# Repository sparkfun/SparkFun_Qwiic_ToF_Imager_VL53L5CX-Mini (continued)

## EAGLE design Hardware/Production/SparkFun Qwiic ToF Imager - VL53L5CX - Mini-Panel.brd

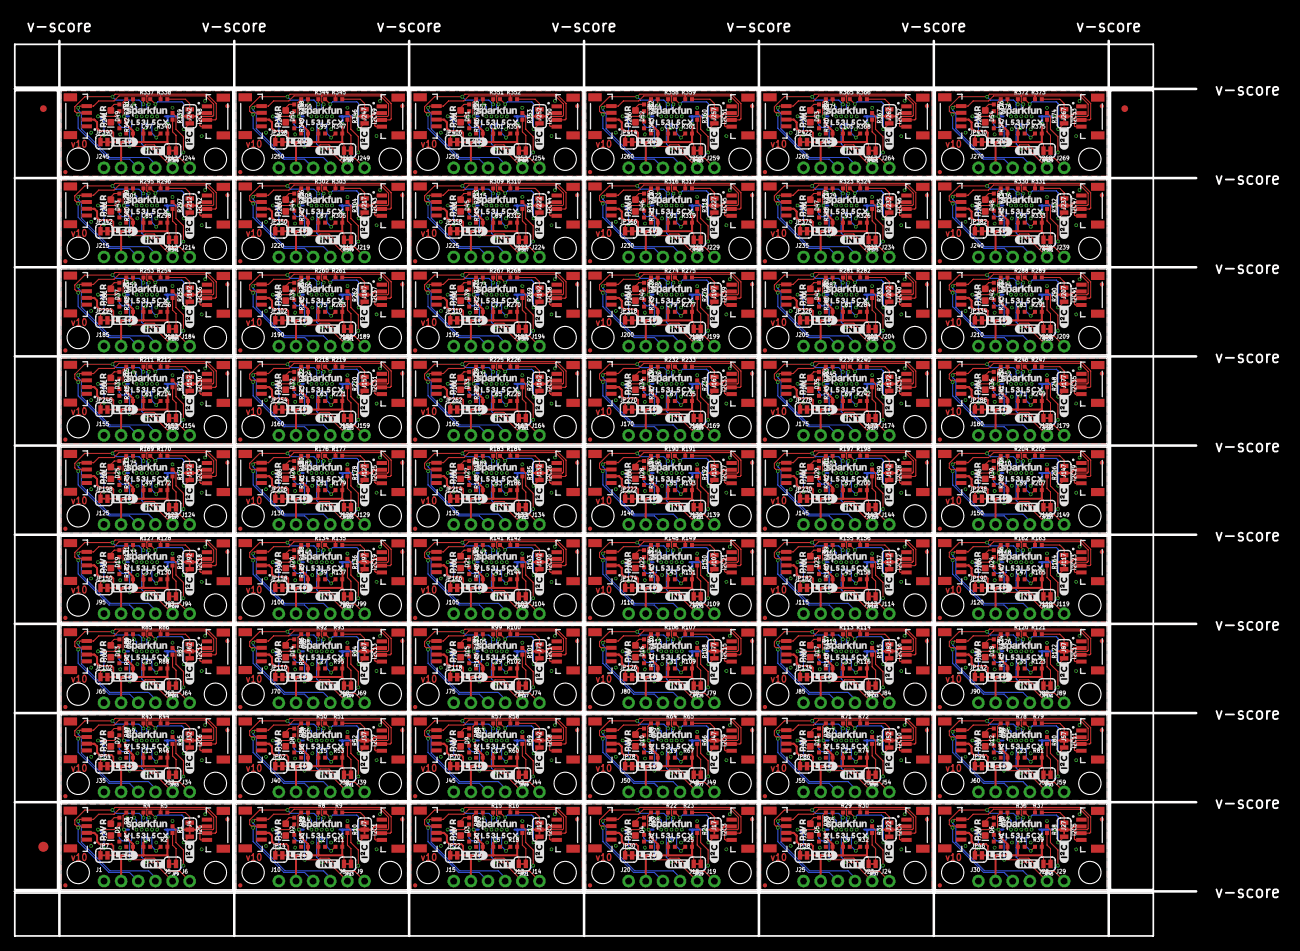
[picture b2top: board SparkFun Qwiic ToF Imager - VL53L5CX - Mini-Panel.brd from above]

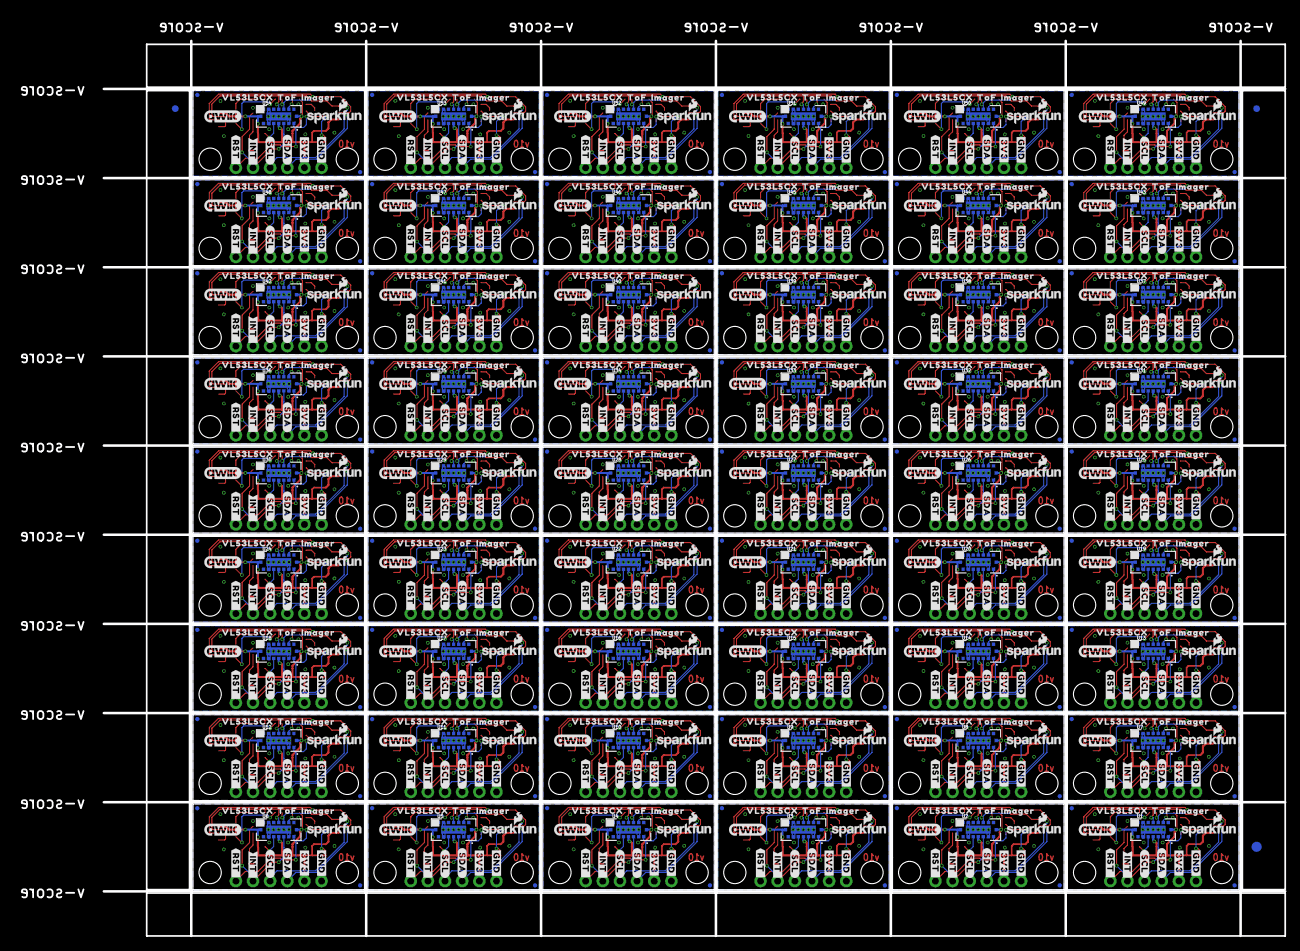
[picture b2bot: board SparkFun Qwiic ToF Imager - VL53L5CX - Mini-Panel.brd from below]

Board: 2 copper layers, 175.0 x 132.6 mm, 2274 parts (759 on the bottom side), 702 nets.

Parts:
C1, C3, C6, C8, C10, C12, C14, C16, C18, C20, C22, C24, C26, C28, C30, C32, C34, C36, C38, C40, C42, C44, C46, C48, C50, C52, C54, C56, C58, C60, C62, C64, C66, C68, C70, C72, C74, C76, C78, C80, C82, C84, C86, C88, C90, C92, C94, C96, C98, C100, C102, C104, C106, C108: 4.7uF; 0402-TIGHT
C2, C4, C5, C7, C9, C11, C13, C15, C17, C19, C21, C23, C25, C27, C29, C31, C33, C35, C37, C39, C41, C43, C45, C47, C49, C51, C53, C55, C57, C59, C61, C63, C65, C67, C69, C71, C73, C75, C77, C79, C81, C83, C85, C87, C89, C91, C93, C95, C97, C99, C101, C103, C105, C107: 0.1uF; 0402-TIGHT
D1, D2, D3, D4, D5, D6, D7, D8, D9, D10, D11, D12, D13, D14, D15, D16, D17, D18, D19, D20, D21, D22, D23, D24, D25, D26, D27, D28, D29, D30, D31, D32, D33, D34, D35, D36, D37, D38, D39, D40, D41, D42, D43, D44, D45, D46, D47, D48, D49, D50, D51, D52, D53, D54: RED; LED-0603
E$1, E$2, E$3, E$4: FIDUCIAL-1X2
E$5, E$6: FIDUCIAL-1.5X3
I2C, I2C1, I2C2, I2C3, I2C4, I2C5, I2C6, I2C7, I2C8, I2C9, I2C10, I2C11, I2C12, I2C13, I2C14, I2C15, I2C16, I2C17, I2C18, I2C19, I2C20, I2C21, I2C22, I2C23, I2C24, I2C25, I2C26, I2C27, I2C28, I2C29, I2C30, I2C31, I2C32, I2C33, I2C34, I2C35, I2C36, I2C37, I2C38, I2C39, I2C40, I2C41, I2C42, I2C43, I2C44, I2C45, I2C46, I2C47, I2C48, I2C49, I2C50, I2C51, I2C52, I2C53: JUMPER-SMT_3_2-NC_TRACE_SILK; SMT-JUMPER_3_2-NC_TRACE_SILK
J1, J10, J15, J20, J25, J30, J35, J40, J45, J50, J55, J60, J65, J70, J75, J80, J85, J90, J95, J100, J105, J110, J115, J120, J125, J130, J135, J140, J145, J150, J155, J160, J165, J170, J175, J180, J185, J190, J195, J200, J205, J210, J215, J220, J225, J230, J235, J240, J245, J250, J255, J260, J265, J270: 1X04_NO_SILK
J2, J3, J4, J7, J11, J12, J16, J17, J21, J22, J26, J27, J31, J32, J36, J37, J41, J42, J46, J47, J51, J52, J56, J57, J61, J62, J66, J67, J71, J72, J76, J77, J81, J82, J86, J87, J91, J92, J96, J97, J101, J102, J106, J107, J111, J112, J116, J117, J121, J122, J126, J127, J131, J132, J136, J137, J141, J142, J146, J147, J151, J152, J156, J157, J161, J162, J166, J167, J171, J172, J176, J177, J181, J182, J186, J187, J191, J192, J196, J197, J201, J202, J206, J207, J211, J212, J216, J217, J221, J222, J226, J227, J231, J232, J236, J237, J241, J242, J246, J247, J251, J252, J256, J257, J261, J262, J266, J267: Vertical Qwiic Connector; JST04_1MM_VERT
J5, J6, J8, J9, J13, J14, J18, J19, J23, J24, J28, J29, J33, J34, J38, J39, J43, J44, J48, J49, J53, J54, J58, J59, J63, J64, J68, J69, J73, J74, J78, J79, J83, J84, J88, J89, J93, J94, J98, J99, J103, J104, J108, J109, J113, J114, J118, J119, J123, J124, J128, J129, J133, J134, J138, J139, J143, J144, J148, J149, J153, J154, J158, J159, J163, J164, J168, J169, J173, J174, J178, J179, J183, J184, J188, J189, J193, J194, J198, J199, J203, J204, J208, J209, J213, J214, J218, J219, J223, J224, J228, J229, J233, J234, J238, J239, J243, J244, J248, J249, J253, J254, J258, J259, J263, J264, J268, J269: 1X01_NO_SILK
JP1, JP2, JP3, JP4, JP5, JP6, JP8, JP12, JP17, JP18, JP19, JP20, JP25, JP26, JP27, JP28, JP33, JP34, JP35, JP36, JP41, JP42, JP43, JP44, JP49, JP50, JP51, JP52, JP57, JP58, JP59, JP60, JP65, JP66, JP67, JP68, JP73, JP74, JP75, JP76, JP81, JP82, JP83, JP84, JP89, JP90, JP91, JP92, JP97, JP98, JP99, JP100, JP105, JP106, JP107, JP108, JP113, JP114, JP115, JP116, JP121, JP122, JP123, JP124, JP129, JP130, JP131, JP132, JP137, JP138, JP139, JP140, JP145, JP146, JP147, JP148, JP153, JP154, JP155, JP156, JP161, JP162, JP163, JP164, JP169, JP170, JP171, JP172, JP177, JP178, JP179, JP180, JP185, JP186, JP187, JP188, JP193, JP194, JP195, JP196, JP201, JP202, JP203, JP204, JP209, JP210, JP211, JP212, JP217, JP218, JP219, JP220, JP225, JP226, JP227, JP228, JP233, JP234, JP235, JP236, JP241, JP242, JP243, JP244, JP249, JP250, JP251, JP252, JP257, JP258, JP259, JP260, JP265, JP266, JP267, JP268, JP273, JP274, JP275, JP276, JP281, JP282, JP283, JP284, JP289, JP290, JP291, JP292, JP297, JP298, JP299, JP300, JP305, JP306, JP307, JP308, JP313, JP314, JP315, JP316, JP321, JP322, JP323, JP324, JP329, JP330, JP331, JP332, JP337, JP338, JP339, JP340, JP345, JP346, JP347, JP348, JP353, JP354, JP355, JP356, JP361, JP362, JP363, JP364, JP369, JP370, JP371, JP372, JP377, JP378, JP379, JP380, JP385, JP386, JP387, JP388, JP393, JP394, JP395, JP396, JP401, JP402, JP403, JP404, JP409, JP410, JP411, JP412, JP417, JP418, JP419, JP420, JP425, JP426, JP427, JP428: FIDUCIALUFIDUCIAL; FIDUCIAL-MICRO
JP7, JP14, JP22, JP30, JP38, JP46, JP54, JP62, JP70, JP78, JP86, JP94, JP102, JP110, JP118, JP126, JP134, JP142, JP150, JP158, JP166, JP174, JP182, JP190, JP198, JP206, JP214, JP222, JP230, JP238, JP246, JP254, JP262, JP270, JP278, JP286, JP294, JP302, JP310, JP318, JP326, JP334, JP342, JP350, JP358, JP366, JP374, JP382, JP390, JP398, JP406, JP414, JP422, JP430: PWR_LED; SMT-JUMPER_2_NC_TRACE_SILK
JP9, JP13, JP21, JP29, JP37, JP45, JP53, JP61, JP69, JP77, JP85, JP93, JP101, JP109, JP117, JP125, JP133, JP141, JP149, JP157, JP165, JP173, JP181, JP189, JP197, JP205, JP213, JP221, JP229, JP237, JP245, JP253, JP261, JP269, JP277, JP285, JP293, JP301, JP309, JP317, JP325, JP333, JP341, JP349, JP357, JP365, JP373, JP381, JP389, JP397, JP405, JP413, JP421, JP429: INT; SMT-JUMPER_2_NC_TRACE_SILK
JP10, JP11, JP15, JP16, JP23, JP24, JP31, JP32, JP39, JP40, JP47, JP48, JP55, JP56, JP63, JP64, JP71, JP72, JP79, JP80, JP87, JP88, JP95, JP96, JP103, JP104, JP111, JP112, JP119, JP120, JP127, JP128, JP135, JP136, JP143, JP144, JP151, JP152, JP159, JP160, JP167, JP168, JP175, JP176, JP183, JP184, JP191, JP192, JP199, JP200, JP207, JP208, JP215, JP216, JP223, JP224, JP231, JP232, JP239, JP240, JP247, JP248, JP255, JP256, JP263, JP264, JP271, JP272, JP279, JP280, JP287, JP288, JP295, JP296, JP303, JP304, JP311, JP312, JP319, JP320, JP327, JP328, JP335, JP336, JP343, JP344, JP351, JP352, JP359, JP360, JP367, JP368, JP375, JP376, JP383, JP384, JP391, JP392, JP399, JP400, JP407, JP408, JP415, JP416, JP423, JP424, JP431, JP432: STAND-OFF
LOGO1, LOGO6, LOGO9, LOGO12, LOGO15, LOGO18, LOGO21, LOGO24, LOGO27, LOGO30, LOGO33, LOGO36, LOGO39, LOGO42, LOGO45, LOGO48, LOGO51, LOGO54, LOGO57, LOGO60, LOGO63, LOGO66, LOGO69, LOGO72, LOGO75, LOGO78, LOGO81, LOGO84, LOGO87, LOGO90, LOGO93, LOGO96, LOGO99, LOGO102, LOGO105, LOGO108, LOGO111, LOGO114, LOGO117, LOGO120, LOGO123, LOGO126, LOGO129, LOGO132, LOGO135, LOGO138, LOGO141, LOGO144, LOGO147, LOGO150, LOGO153, LOGO156, LOGO159, LOGO162: SFE_LOGO_NAME_FLAME8_MM; SFE_LOGO_NAME_FLAME_8MM
LOGO2, LOGO3, LOGO7, LOGO10, LOGO13, LOGO16, LOGO19, LOGO22, LOGO25, LOGO28, LOGO31, LOGO34, LOGO37, LOGO40, LOGO43, LOGO46, LOGO49, LOGO52, LOGO55, LOGO58, LOGO61, LOGO64, LOGO67, LOGO70, LOGO73, LOGO76, LOGO79, LOGO82, LOGO85, LOGO88, LOGO91, LOGO94, LOGO97, LOGO100, LOGO103, LOGO106, LOGO109, LOGO112, LOGO115, LOGO118, LOGO121, LOGO124, LOGO127, LOGO130, LOGO133, LOGO136, LOGO139, LOGO142, LOGO145, LOGO148, LOGO151, LOGO154, LOGO157, LOGO160: QWIIC_LOGO_CONNECTOR; QWIIC_5.5MM
LOGO4, LOGO5, LOGO8, LOGO11, LOGO14, LOGO17, LOGO20, LOGO23, LOGO26, LOGO29, LOGO32, LOGO35, LOGO38, LOGO41, LOGO44, LOGO47, LOGO50, LOGO53, LOGO56, LOGO59, LOGO62, LOGO65, LOGO68, LOGO71, LOGO74, LOGO77, LOGO80, LOGO83, LOGO86, LOGO89, LOGO92, LOGO95, LOGO98, LOGO101, LOGO104, LOGO107, LOGO110, LOGO113, LOGO116, LOGO119, LOGO122, LOGO125, LOGO128, LOGO131, LOGO134, LOGO137, LOGO140, LOGO143, LOGO146, LOGO149, LOGO152, LOGO155, LOGO158, LOGO161: SFE_LOGO_NAME6_MM; SFE_LOGO_NAME_6MM
R1, R2, R6, R7, R10, R11, R13, R14, R17, R18, R20, R21, R24, R25, R27, R28, R31, R32, R34, R35, R38, R39, R41, R42, R45, R46, R48, R49, R52, R53, R55, R56, R59, R60, R62, R63, R66, R67, R69, R70, R73, R74, R76, R77, R80, R81, R83, R84, R87, R88, R90, R91, R94, R95, R97, R98, R101, R102, R104, R105, R108, R109, R111, R112, R115, R116, R118, R119, R122, R123, R125, R126, R129, R130, R132, R133, R136, R137, R139, R140, R143, R144, R146, R147, R150, R151, R153, R154, R157, R158, R160, R161, R164, R165, R167, R168, R171, R172, R174, R175, R178, R179, R181, R182, R185, R186, R188, R189, R192, R193, R195, R196, R199, R200, R202, R203, R206, R207, R209, R210, R213, R214, R216, R217, R220, R221, R223, R224, R227, R228, R230, R231, R234, R235, R237, R238, R241, R242, R244, R245, R248, R249, R251, R252, R255, R256, R258, R259, R262, R263, R265, R266, R269, R270, R272, R273, R276, R277, R279, R280, R283, R284, R286, R287, R290, R291, R293, R294, R297, R298, R300, R301, R304, R305, R307, R308, R311, R312, R314, R315, R318, R319, R321, R322, R325, R326, R328, R329, R332, R333, R335, R336, R339, R340, R342, R343, R346, R347, R349, R350, R353, R354, R356, R357, R360, R361, R363, R364, R367, R368, R370, R371, R374, R375, R377, R378: 47k; 0402-TIGHT
R3, R12, R19, R26, R33, R40, R47, R54, R61, R68, R75, R82, R89, R96, R103, R110, R117, R124, R131, R138, R145, R152, R159, R166, R173, R180, R187, R194, R201, R208, R215, R222, R229, R236, R243, R250, R257, R264, R271, R278, R285, R292, R299, R306, R313, R320, R327, R334, R341, R348, R355, R362, R369, R376: 1k; 0402-TIGHT
R4, R5, R8, R9, R15, R16, R22, R23, R29, R30, R36, R37, R43, R44, R50, R51, R57, R58, R64, R65, R71, R72, R78, R79, R85, R86, R92, R93, R99, R100, R106, R107, R113, R114, R120, R121, R127, R128, R134, R135, R141, R142, R148, R149, R155, R156, R162, R163, R169, R170, R176, R177, R183, R184, R190, R191, R197, R198, R204, R205, R211, R212, R218, R219, R225, R226, R232, R233, R239, R240, R246, R247, R253, R254, R260, R261, R267, R268, R274, R275, R281, R282, R288, R289, R295, R296, R302, R303, R309, R310, R316, R317, R323, R324, R330, R331, R337, R338, R344, R345, R351, R352, R358, R359, R365, R366, R372, R373: 2.2k; 0402-TIGHT
U1, U2, U3, U4, U5, U6, U7, U8, U9, U10, U11, U12, U13, U14, U15, U16, U17, U18, U19, U20, U21, U22, U23, U24, U25, U26, U27, U28, U29, U30, U31, U32, U33, U34, U35, U36, U37, U38, U39, U40, U41, U42, U43, U44, U45, U46, U47, U48, U49, U50, U51, U52, U53, U54: VL53L5CX
U$1, U$23, U$40, U$54, U$68, U$82, U$96, U$110, U$124, U$138, U$152, U$166, U$180, U$194, U$208, U$222, U$236, U$250, U$264, U$278, U$292, U$306, U$320, U$334, U$348, U$362, U$376, U$390, U$404, U$418, U$432, U$446, U$460, U$474, U$488, U$502, U$516, U$530, U$544, U$558, U$572, U$586, U$600, U$614, U$628, U$642, U$656, U$670, U$684, U$698, U$712, U$726, U$740, U$754: VL53L5CX_0
U$2, U$26, U$41, U$55, U$69, U$83, U$97, U$111, U$125, U$139, U$153, U$167, U$181, U$195, U$209, U$223, U$237, U$251, U$265, U$279, U$293, U$307, U$321, U$335, U$349, U$363, U$377, U$391, U$405, U$419, U$433, U$447, U$461, U$475, U$489, U$503, U$517, U$531, U$545, U$559, U$573, U$587, U$601, U$615, U$629, U$643, U$657, U$671, U$685, U$699, U$713, U$727, U$741, U$755: #LED#0
U$3, U$7, U$29, U$44, U$58, U$72, U$86, U$100, U$114, U$128, U$142, U$156, U$170, U$184, U$198, U$212, U$226, U$240, U$254, U$268, U$282, U$296, U$310, U$324, U$338, U$352, U$366, U$380, U$394, U$408, U$422, U$436, U$450, U$464, U$478, U$492, U$506, U$520, U$534, U$548, U$562, U$576, U$590, U$604, U$618, U$632, U$646, U$660, U$674, U$688, U$702, U$716, U$730, U$744: #3V3#13
U$4, U$10, U$31, U$45, U$59, U$73, U$87, U$101, U$115, U$129, U$143, U$157, U$171, U$185, U$199, U$213, U$227, U$241, U$255, U$269, U$283, U$297, U$311, U$325, U$339, U$353, U$367, U$381, U$395, U$409, U$423, U$437, U$451, U$465, U$479, U$493, U$507, U$521, U$535, U$549, U$563, U$577, U$591, U$605, U$619, U$633, U$647, U$661, U$675, U$689, U$703, U$717, U$731, U$745: PWR12
U$5, U$27, U$42, U$56, U$70, U$84, U$98, U$112, U$126, U$140, U$154, U$168, U$182, U$196, U$210, U$224, U$238, U$252, U$266, U$280, U$294, U$308, U$322, U$336, U$350, U$364, U$378, U$392, U$406, U$420, U$434, U$448, U$462, U$476, U$490, U$504, U$518, U$532, U$546, U$560, U$574, U$588, U$602, U$616, U$630, U$644, U$658, U$672, U$686, U$700, U$714, U$728, U$742, U$756: #INT#0
U$6, U$28, U$30, U$43, U$57, U$71, U$85, U$99, U$113, U$127, U$141, U$155, U$169, U$183, U$197, U$211, U$225, U$239, U$253, U$267, U$281, U$295, U$309, U$323, U$337, U$351, U$365, U$379, U$393, U$407, U$421, U$435, U$449, U$463, U$477, U$491, U$505, U$519, U$533, U$547, U$561, U$575, U$589, U$603, U$617, U$631, U$645, U$659, U$673, U$687, U$701, U$715, U$729, U$743: #GND#62130
U$8, U$11, U$32, U$46, U$60, U$74, U$88, U$102, U$116, U$130, U$144, U$158, U$172, U$186, U$200, U$214, U$228, U$242, U$256, U$270, U$284, U$298, U$312, U$326, U$340, U$354, U$368, U$382, U$396, U$410, U$424, U$438, U$452, U$466, U$480, U$494, U$508, U$522, U$536, U$550, U$564, U$578, U$592, U$606, U$620, U$634, U$648, U$662, U$676, U$690, U$704, U$718, U$732, U$746: #INT_#0
U$9, U$12, U$33, U$47, U$61, U$75, U$89, U$103, U$117, U$131, U$145, U$159, U$173, U$187, U$201, U$215, U$229, U$243, U$257, U$271, U$285, U$299, U$313, U$327, U$341, U$355, U$369, U$383, U$397, U$411, U$425, U$439, U$453, U$467, U$481, U$495, U$509, U$523, U$537, U$551, U$565, U$579, U$593, U$607, U$621, U$635, U$649, U$663, U$677, U$691, U$705, U$719, U$733, U$747: #RST_#1
U$13, U$16, U$34, U$48, U$62, U$76, U$90, U$104, U$118, U$132, U$146, U$160, U$174, U$188, U$202, U$216, U$230, U$244, U$258, U$272, U$286, U$300, U$314, U$328, U$342, U$356, U$370, U$384, U$398, U$412, U$426, U$440, U$454, U$468, U$482, U$496, U$510, U$524, U$538, U$552, U$566, U$580, U$594, U$608, U$622, U$636, U$650, U$664, U$678, U$692, U$706, U$720, U$734, U$748: #I�C#0
U$14, U$19, U$35, U$49, U$63, U$77, U$91, U$105, U$119, U$133, U$147, U$161, U$175, U$189, U$203, U$217, U$231, U$245, U$259, U$273, U$287, U$301, U$315, U$329, U$343, U$357, U$371, U$385, U$399, U$413, U$427, U$441, U$455, U$469, U$483, U$497, U$511, U$525, U$539, U$553, U$567, U$581, U$595, U$609, U$623, U$637, U$651, U$665, U$679, U$693, U$707, U$721, U$735, U$749: VL53L5CX0
U$15, U$20, U$36, U$50, U$64, U$78, U$92, U$106, U$120, U$134, U$148, U$162, U$176, U$190, U$204, U$218, U$232, U$246, U$260, U$274, U$288, U$302, U$316, U$330, U$344, U$358, U$372, U$386, U$400, U$414, U$428, U$442, U$456, U$470, U$484, U$498, U$512, U$526, U$540, U$554, U$568, U$582, U$596, U$610, U$624, U$638, U$652, U$666, U$680, U$694, U$708, U$722, U$736, U$750: TOF1
U$17, U$22, U$37, U$51, U$65, U$79, U$93, U$107, U$121, U$135, U$149, U$163, U$177, U$191, U$205, U$219, U$233, U$247, U$261, U$275, U$289, U$303, U$317, U$331, U$345, U$359, U$373, U$387, U$401, U$415, U$429, U$443, U$457, U$471, U$485, U$499, U$513, U$527, U$541, U$555, U$569, U$583, U$597, U$611, U$625, U$639, U$653, U$667, U$681, U$695, U$709, U$723, U$737, U$751: IMAGER2
U$18, U$24, U$38, U$52, U$66, U$80, U$94, U$108, U$122, U$136, U$150, U$164, U$178, U$192, U$206, U$220, U$234, U$248, U$262, U$276, U$290, U$304, U$318, U$332, U$346, U$360, U$374, U$388, U$402, U$416, U$430, U$444, U$458, U$472, U$486, U$500, U$514, U$528, U$542, U$556, U$570, U$584, U$598, U$612, U$626, U$640, U$654, U$668, U$682, U$696, U$710, U$724, U$738, U$752: #SCL#1
U$21, U$25, U$39, U$53, U$67, U$81, U$95, U$109, U$123, U$137, U$151, U$165, U$179, U$193, U$207, U$221, U$235, U$249, U$263, U$277, U$291, U$305, U$319, U$333, U$347, U$361, U$375, U$389, U$403, U$417, U$431, U$445, U$459, U$473, U$487, U$501, U$515, U$529, U$543, U$557, U$571, U$585, U$599, U$613, U$627, U$641, U$655, U$669, U$683, U$697, U$711, U$725, U$739, U$753: #SDA#0

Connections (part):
3.3V: C1.1, C4.1, I2C.2, J1.2, J2.2, J4.2, JP7.2, JP9.2, R2.2, R7.2, U1.A4, U1.B1, U1.B7
3.3V1: C2.1, C3.1, I2C1.2, J3.2, J7.2, J10.2, JP13.2, JP14.2, R11.2, R14.2, U2.A4, U2.B1, U2.B7
3.3V2: C5.1, C6.1, I2C2.2, J11.2, J12.2, J15.2, JP21.2, JP22.2, R18.2, R21.2, U3.A4, U3.B1, U3.B7
3.3V3: C7.1, C8.1, I2C3.2, J16.2, J17.2, J20.2, JP29.2, JP30.2, R25.2, R28.2, U4.A4, U4.B1, U4.B7
3.3V4: C9.1, C10.1, I2C4.2, J21.2, J22.2, J25.2, JP37.2, JP38.2, R32.2, R35.2, U5.A4, U5.B1, U5.B7
3.3V5: C11.1, C12.1, I2C5.2, J26.2, J27.2, J30.2, JP45.2, JP46.2, R39.2, R42.2, U6.A4, U6.B1, U6.B7
3.3V6: C13.1, C14.1, I2C6.2, J31.2, J32.2, J35.2, JP53.2, JP54.2, R46.2, R49.2, U7.A4, U7.B1, U7.B7
3.3V7: C15.1, C16.1, I2C7.2, J36.2, J37.2, J40.2, JP61.2, JP62.2, R53.2, R56.2, U8.A4, U8.B1, U8.B7
3.3V8: C17.1, C18.1, I2C8.2, J41.2, J42.2, J45.2, JP69.2, JP70.2, R60.2, R63.2, U9.A4, U9.B1, U9.B7
3.3V9: C19.1, C20.1, I2C9.2, J46.2, J47.2, J50.2, JP77.2, JP78.2, R67.2, R70.2, U10.A4, U10.B1, U10.B7
3.3V10: C21.1, C22.1, I2C10.2, J51.2, J52.2, J55.2, JP85.2, JP86.2, R74.2, R77.2, U11.A4, U11.B1, U11.B7
3.3V11: C23.1, C24.1, I2C11.2, J56.2, J57.2, J60.2, JP93.2, JP94.2, R81.2, R84.2, U12.A4, U12.B1, U12.B7
3.3V12: C25.1, C26.1, I2C12.2, J61.2, J62.2, J65.2, JP101.2, JP102.2, R88.2, R91.2, U13.A4, U13.B1, U13.B7
3.3V13: C27.1, C28.1, I2C13.2, J66.2, J67.2, J70.2, JP109.2, JP110.2, R95.2, R98.2, U14.A4, U14.B1, U14.B7
3.3V14: C29.1, C30.1, I2C14.2, J71.2, J72.2, J75.2, JP117.2, JP118.2, R102.2, R105.2, U15.A4, U15.B1, U15.B7
3.3V15: C31.1, C32.1, I2C15.2, J76.2, J77.2, J80.2, JP125.2, JP126.2, R109.2, R112.2, U16.A4, U16.B1, U16.B7
3.3V16: C33.1, C34.1, I2C16.2, J81.2, J82.2, J85.2, JP133.2, JP134.2, R116.2, R119.2, U17.A4, U17.B1, U17.B7
3.3V17: C35.1, C36.1, I2C17.2, J86.2, J87.2, J90.2, JP141.2, JP142.2, R123.2, R126.2, U18.A4, U18.B1, U18.B7
3.3V18: C37.1, C38.1, I2C18.2, J91.2, J92.2, J95.2, JP149.2, JP150.2, R130.2, R133.2, U19.A4, U19.B1, U19.B7
3.3V19: C39.1, C40.1, I2C19.2, J96.2, J97.2, J100.2, JP157.2, JP158.2, R137.2, R140.2, U20.A4, U20.B1, U20.B7
3.3V20: C41.1, C42.1, I2C20.2, J101.2, J102.2, J105.2, JP165.2, JP166.2, R144.2, R147.2, U21.A4, U21.B1, U21.B7
3.3V21: C43.1, C44.1, I2C21.2, J106.2, J107.2, J110.2, JP173.2, JP174.2, R151.2, R154.2, U22.A4, U22.B1, U22.B7
3.3V22: C45.1, C46.1, I2C22.2, J111.2, J112.2, J115.2, JP181.2, JP182.2, R158.2, R161.2, U23.A4, U23.B1, U23.B7
3.3V23: C47.1, C48.1, I2C23.2, J116.2, J117.2, J120.2, JP189.2, JP190.2, R165.2, R168.2, U24.A4, U24.B1, U24.B7
3.3V24: C49.1, C50.1, I2C24.2, J121.2, J122.2, J125.2, JP197.2, JP198.2, R172.2, R175.2, U25.A4, U25.B1, U25.B7
3.3V25: C51.1, C52.1, I2C25.2, J126.2, J127.2, J130.2, JP205.2, JP206.2, R179.2, R182.2, U26.A4, U26.B1, U26.B7
3.3V26: C53.1, C54.1, I2C26.2, J131.2, J132.2, J135.2, JP213.2, JP214.2, R186.2, R189.2, U27.A4, U27.B1, U27.B7
3.3V27: C55.1, C56.1, I2C27.2, J136.2, J137.2, J140.2, JP221.2, JP222.2, R193.2, R196.2, U28.A4, U28.B1, U28.B7
3.3V28: C57.1, C58.1, I2C28.2, J141.2, J142.2, J145.2, JP229.2, JP230.2, R200.2, R203.2, U29.A4, U29.B1, U29.B7
3.3V29: C59.1, C60.1, I2C29.2, J146.2, J147.2, J150.2, JP237.2, JP238.2, R207.2, R210.2, U30.A4, U30.B1, U30.B7
3.3V30: C61.1, C62.1, I2C30.2, J151.2, J152.2, J155.2, JP245.2, JP246.2, R214.2, R217.2, U31.A4, U31.B1, U31.B7
3.3V31: C63.1, C64.1, I2C31.2, J156.2, J157.2, J160.2, JP253.2, JP254.2, R221.2, R224.2, U32.A4, U32.B1, U32.B7
3.3V32: C65.1, C66.1, I2C32.2, J161.2, J162.2, J165.2, JP261.2, JP262.2, R228.2, R231.2, U33.A4, U33.B1, U33.B7
3.3V33: C67.1, C68.1, I2C33.2, J166.2, J167.2, J170.2, JP269.2, JP270.2, R235.2, R238.2, U34.A4, U34.B1, U34.B7
3.3V34: C69.1, C70.1, I2C34.2, J171.2, J172.2, J175.2, JP277.2, JP278.2, R242.2, R245.2, U35.A4, U35.B1, U35.B7
3.3V35: C71.1, C72.1, I2C35.2, J176.2, J177.2, J180.2, JP285.2, JP286.2, R249.2, R252.2, U36.A4, U36.B1, U36.B7
3.3V36: C73.1, C74.1, I2C36.2, J181.2, J182.2, J185.2, JP293.2, JP294.2, R256.2, R259.2, U37.A4, U37.B1, U37.B7
3.3V37: C75.1, C76.1, I2C37.2, J186.2, J187.2, J190.2, JP301.2, JP302.2, R263.2, R266.2, U38.A4, U38.B1, U38.B7
3.3V38: C77.1, C78.1, I2C38.2, J191.2, J192.2, J195.2, JP309.2, JP310.2, R270.2, R273.2, U39.A4, U39.B1, U39.B7
3.3V39: C79.1, C80.1, I2C39.2, J196.2, J197.2, J200.2, JP317.2, JP318.2, R277.2, R280.2, U40.A4, U40.B1, U40.B7
3.3V40: C81.1, C82.1, I2C40.2, J201.2, J202.2, J205.2, JP325.2, JP326.2, R284.2, R287.2, U41.A4, U41.B1, U41.B7
3.3V41: C83.1, C84.1, I2C41.2, J206.2, J207.2, J210.2, JP333.2, JP334.2, R291.2, R294.2, U42.A4, U42.B1, U42.B7
3.3V42: C85.1, C86.1, I2C42.2, J211.2, J212.2, J215.2, JP341.2, JP342.2, R298.2, R301.2, U43.A4, U43.B1, U43.B7
3.3V43: C87.1, C88.1, I2C43.2, J216.2, J217.2, J220.2, JP349.2, JP350.2, R305.2, R308.2, U44.A4, U44.B1, U44.B7
3.3V44: C89.1, C90.1, I2C44.2, J221.2, J222.2, J225.2, JP357.2, JP358.2, R312.2, R315.2, U45.A4, U45.B1, U45.B7
3.3V45: C91.1, C92.1, I2C45.2, J226.2, J227.2, J230.2, JP365.2, JP366.2, R319.2, R322.2, U46.A4, U46.B1, U46.B7
3.3V46: C93.1, C94.1, I2C46.2, J231.2, J232.2, J235.2, JP373.2, JP374.2, R326.2, R329.2, U47.A4, U47.B1, U47.B7
3.3V47: C95.1, C96.1, I2C47.2, J236.2, J237.2, J240.2, JP381.2, JP382.2, R333.2, R336.2, U48.A4, U48.B1, U48.B7
3.3V48: C97.1, C98.1, I2C48.2, J241.2, J242.2, J245.2, JP389.2, JP390.2, R340.2, R343.2, U49.A4, U49.B1, U49.B7
3.3V49: C99.1, C100.1, I2C49.2, J246.2, J247.2, J250.2, JP397.2, JP398.2, R347.2, R350.2, U50.A4, U50.B1, U50.B7
3.3V50: C101.1, C102.1, I2C50.2, J251.2, J252.2, J255.2, JP405.2, JP406.2, R354.2, R357.2, U51.A4, U51.B1, U51.B7
3.3V51: C103.1, C104.1, I2C51.2, J256.2, J257.2, J260.2, JP413.2, JP414.2, R361.2, R364.2, U52.A4, U52.B1, U52.B7
3.3V52: C105.1, C106.1, I2C52.2, J261.2, J262.2, J265.2, JP421.2, JP422.2, R368.2, R371.2, U53.A4, U53.B1, U53.B7
3.3V53: C107.1, C108.1, I2C53.2, J266.2, J267.2, J270.2, JP429.2, JP430.2, R375.2, R378.2, U54.A4, U54.B1, U54.B7
!LP: R2.1, U1.A5
!LP1: R11.1, U2.A5
!LP2: R18.1, U3.A5
!LP3: R25.1, U4.A5
!LP4: R32.1, U5.A5
!LP5: R39.1, U6.A5
!LP6: R46.1, U7.A5
!LP7: R53.1, U8.A5
!LP8: R60.1, U9.A5
!LP9: R67.1, U10.A5
!LP10: R74.1, U11.A5
!LP11: R81.1, U12.A5
!LP12: R88.1, U13.A5
!LP13: R95.1, U14.A5
!LP14: R102.1, U15.A5
!LP15: R109.1, U16.A5
!LP16: R116.1, U17.A5
!LP17: R123.1, U18.A5
!LP18: R130.1, U19.A5
!LP19: R137.1, U20.A5
!LP20: R144.1, U21.A5
!LP21: R151.1, U22.A5
!LP22: R158.1, U23.A5
!LP23: R165.1, U24.A5
!LP24: R172.1, U25.A5
!LP25: R179.1, U26.A5
!LP26: R186.1, U27.A5
!LP27: R193.1, U28.A5
!LP28: R200.1, U29.A5
!LP29: R207.1, U30.A5
!LP30: R214.1, U31.A5
!LP31: R221.1, U32.A5
!LP32: R228.1, U33.A5
!LP33: R235.1, U34.A5
!LP34: R242.1, U35.A5
!LP35: R249.1, U36.A5
!LP36: R256.1, U37.A5
!LP37: R263.1, U38.A5
!LP38: R270.1, U39.A5
!LP39: R277.1, U40.A5
!LP40: R284.1, U41.A5
!LP41: R291.1, U42.A5
!LP42: R298.1, U43.A5
!LP43: R305.1, U44.A5
!LP44: R312.1, U45.A5
!LP45: R319.1, U46.A5
!LP46: R326.1, U47.A5
!LP47: R333.1, U48.A5
!LP48: R340.1, U49.A5
!LP49: R347.1, U50.A5
!LP50: R354.1, U51.A5
!LP51: R361.1, U52.A5
!LP52: R368.1, U53.A5
!LP53: R375.1, U54.A5
GND: C1.2, C4.2, D1.C, J1.1, J2.1, J4.1, R6.2, U1.A2, U1.A6, U1.A7, U1.B4, U1.C1, U1.C6, U1.C7
GND1: C2.2, C3.2, D2.C, J3.1, J7.1, J10.1, R13.2, U2.A2, U2.A6, U2.A7, U2.B4, U2.C1, U2.C6, U2.C7
GND2: C5.2, C6.2, D3.C, J11.1, J12.1, J15.1, R20.2, U3.A2, U3.A6, U3.A7, U3.B4, U3.C1, U3.C6, U3.C7
GND3: C7.2, C8.2, D4.C, J16.1, J17.1, J20.1, R27.2, U4.A2, U4.A6, U4.A7, U4.B4, U4.C1, U4.C6, U4.C7
GND4: C9.2, C10.2, D5.C, J21.1, J22.1, J25.1, R34.2, U5.A2, U5.A6, U5.A7, U5.B4, U5.C1, U5.C6, U5.C7
GND5: C11.2, C12.2, D6.C, J26.1, J27.1, J30.1, R41.2, U6.A2, U6.A6, U6.A7, U6.B4, U6.C1, U6.C6, U6.C7
GND6: C13.2, C14.2, D7.C, J31.1, J32.1, J35.1, R48.2, U7.A2, U7.A6, U7.A7, U7.B4, U7.C1, U7.C6, U7.C7
GND7: C15.2, C16.2, D8.C, J36.1, J37.1, J40.1, R55.2, U8.A2, U8.A6, U8.A7, U8.B4, U8.C1, U8.C6, U8.C7
GND8: C17.2, C18.2, D9.C, J41.1, J42.1, J45.1, R62.2, U9.A2, U9.A6, U9.A7, U9.B4, U9.C1, U9.C6, U9.C7
GND9: C19.2, C20.2, D10.C, J46.1, J47.1, J50.1, R69.2, U10.A2, U10.A6, U10.A7, U10.B4, U10.C1, U10.C6, U10.C7
GND10: C21.2, C22.2, D11.C, J51.1, J52.1, J55.1, R76.2, U11.A2, U11.A6, U11.A7, U11.B4, U11.C1, U11.C6, U11.C7
GND11: C23.2, C24.2, D12.C, J56.1, J57.1, J60.1, R83.2, U12.A2, U12.A6, U12.A7, U12.B4, U12.C1, U12.C6, U12.C7
GND12: C25.2, C26.2, D13.C, J61.1, J62.1, J65.1, R90.2, U13.A2, U13.A6, U13.A7, U13.B4, U13.C1, U13.C6, U13.C7
GND13: C27.2, C28.2, D14.C, J66.1, J67.1, J70.1, R97.2, U14.A2, U14.A6, U14.A7, U14.B4, U14.C1, U14.C6, U14.C7
GND14: C29.2, C30.2, D15.C, J71.1, J72.1, J75.1, R104.2, U15.A2, U15.A6, U15.A7, U15.B4, U15.C1, U15.C6, U15.C7
GND15: C31.2, C32.2, D16.C, J76.1, J77.1, J80.1, R111.2, U16.A2, U16.A6, U16.A7, U16.B4, U16.C1, U16.C6, U16.C7
GND16: C33.2, C34.2, D17.C, J81.1, J82.1, J85.1, R118.2, U17.A2, U17.A6, U17.A7, U17.B4, U17.C1, U17.C6, U17.C7
GND17: C35.2, C36.2, D18.C, J86.1, J87.1, J90.1, R125.2, U18.A2, U18.A6, U18.A7, U18.B4, U18.C1, U18.C6, U18.C7
GND18: C37.2, C38.2, D19.C, J91.1, J92.1, J95.1, R132.2, U19.A2, U19.A6, U19.A7, U19.B4, U19.C1, U19.C6, U19.C7
GND19: C39.2, C40.2, D20.C, J96.1, J97.1, J100.1, R139.2, U20.A2, U20.A6, U20.A7, U20.B4, U20.C1, U20.C6, U20.C7
GND20: C41.2, C42.2, D21.C, J101.1, J102.1, J105.1, R146.2, U21.A2, U21.A6, U21.A7, U21.B4, U21.C1, U21.C6, U21.C7
GND21: C43.2, C44.2, D22.C, J106.1, J107.1, J110.1, R153.2, U22.A2, U22.A6, U22.A7, U22.B4, U22.C1, U22.C6, U22.C7
GND22: C45.2, C46.2, D23.C, J111.1, J112.1, J115.1, R160.2, U23.A2, U23.A6, U23.A7, U23.B4, U23.C1, U23.C6, U23.C7
GND23: C47.2, C48.2, D24.C, J116.1, J117.1, J120.1, R167.2, U24.A2, U24.A6, U24.A7, U24.B4, U24.C1, U24.C6, U24.C7
GND24: C49.2, C50.2, D25.C, J121.1, J122.1, J125.1, R174.2, U25.A2, U25.A6, U25.A7, U25.B4, U25.C1, U25.C6, U25.C7
GND25: C51.2, C52.2, D26.C, J126.1, J127.1, J130.1, R181.2, U26.A2, U26.A6, U26.A7, U26.B4, U26.C1, U26.C6, U26.C7
GND26: C53.2, C54.2, D27.C, J131.1, J132.1, J135.1, R188.2, U27.A2, U27.A6, U27.A7, U27.B4, U27.C1, U27.C6, U27.C7
GND27: C55.2, C56.2, D28.C, J136.1, J137.1, J140.1, R195.2, U28.A2, U28.A6, U28.A7, U28.B4, U28.C1, U28.C6, U28.C7
GND28: C57.2, C58.2, D29.C, J141.1, J142.1, J145.1, R202.2, U29.A2, U29.A6, U29.A7, U29.B4, U29.C1, U29.C6, U29.C7
GND29: C59.2, C60.2, D30.C, J146.1, J147.1, J150.1, R209.2, U30.A2, U30.A6, U30.A7, U30.B4, U30.C1, U30.C6, U30.C7
GND30: C61.2, C62.2, D31.C, J151.1, J152.1, J155.1, R216.2, U31.A2, U31.A6, U31.A7, U31.B4, U31.C1, U31.C6, U31.C7
GND31: C63.2, C64.2, D32.C, J156.1, J157.1, J160.1, R223.2, U32.A2, U32.A6, U32.A7, U32.B4, U32.C1, U32.C6, U32.C7
GND32: C65.2, C66.2, D33.C, J161.1, J162.1, J165.1, R230.2, U33.A2, U33.A6, U33.A7, U33.B4, U33.C1, U33.C6, U33.C7
GND33: C67.2, C68.2, D34.C, J166.1, J167.1, J170.1, R237.2, U34.A2, U34.A6, U34.A7, U34.B4, U34.C1, U34.C6, U34.C7
GND34: C69.2, C70.2, D35.C, J171.1, J172.1, J175.1, R244.2, U35.A2, U35.A6, U35.A7, U35.B4, U35.C1, U35.C6, U35.C7
GND35: C71.2, C72.2, D36.C, J176.1, J177.1, J180.1, R251.2, U36.A2, U36.A6, U36.A7, U36.B4, U36.C1, U36.C6, U36.C7
GND36: C73.2, C74.2, D37.C, J181.1, J182.1, J185.1, R258.2, U37.A2, U37.A6, U37.A7, U37.B4, U37.C1, U37.C6, U37.C7
GND37: C75.2, C76.2, D38.C, J186.1, J187.1, J190.1, R265.2, U38.A2, U38.A6, U38.A7, U38.B4, U38.C1, U38.C6, U38.C7
GND38: C77.2, C78.2, D39.C, J191.1, J192.1, J195.1, R272.2, U39.A2, U39.A6, U39.A7, U39.B4, U39.C1, U39.C6, U39.C7
GND39: C79.2, C80.2, D40.C, J196.1, J197.1, J200.1, R279.2, U40.A2, U40.A6, U40.A7, U40.B4, U40.C1, U40.C6, U40.C7
GND40: C81.2, C82.2, D41.C, J201.1, J202.1, J205.1, R286.2, U41.A2, U41.A6, U41.A7, U41.B4, U41.C1, U41.C6, U41.C7
GND41: C83.2, C84.2, D42.C, J206.1, J207.1, J210.1, R293.2, U42.A2, U42.A6, U42.A7, U42.B4, U42.C1, U42.C6, U42.C7
GND42: C85.2, C86.2, D43.C, J211.1, J212.1, J215.1, R300.2, U43.A2, U43.A6, U43.A7, U43.B4, U43.C1, U43.C6, U43.C7
GND43: C87.2, C88.2, D44.C, J216.1, J217.1, J220.1, R307.2, U44.A2, U44.A6, U44.A7, U44.B4, U44.C1, U44.C6, U44.C7
GND44: C89.2, C90.2, D45.C, J221.1, J222.1, J225.1, R314.2, U45.A2, U45.A6, U45.A7, U45.B4, U45.C1, U45.C6, U45.C7
GND45: C91.2, C92.2, D46.C, J226.1, J227.1, J230.1, R321.2, U46.A2, U46.A6, U46.A7, U46.B4, U46.C1, U46.C6, U46.C7
GND46: C93.2, C94.2, D47.C, J231.1, J232.1, J235.1, R328.2, U47.A2, U47.A6, U47.A7, U47.B4, U47.C1, U47.C6, U47.C7
GND47: C95.2, C96.2, D48.C, J236.1, J237.1, J240.1, R335.2, U48.A2, U48.A6, U48.A7, U48.B4, U48.C1, U48.C6, U48.C7
GND48: C97.2, C98.2, D49.C, J241.1, J242.1, J245.1, R342.2, U49.A2, U49.A6, U49.A7, U49.B4, U49.C1, U49.C6, U49.C7
GND49: C99.2, C100.2, D50.C, J246.1, J247.1, J250.1, R349.2, U50.A2, U50.A6, U50.A7, U50.B4, U50.C1, U50.C6, U50.C7
GND50: C101.2, C102.2, D51.C, J251.1, J252.1, J255.1, R356.2, U51.A2, U51.A6, U51.A7, U51.B4, U51.C1, U51.C6, U51.C7
GND51: C103.2, C104.2, D52.C, J256.1, J257.1, J260.1, R363.2, U52.A2, U52.A6, U52.A7, U52.B4, U52.C1, U52.C6, U52.C7
GND52: C105.2, C106.2, D53.C, J261.1, J262.1, J265.1, R370.2, U53.A2, U53.A6, U53.A7, U53.B4, U53.C1, U53.C6, U53.C7
GND53: C107.2, C108.2, D54.C, J266.1, J267.1, J270.1, R377.2, U54.A2, U54.A6, U54.A7, U54.B4, U54.C1, U54.C6, U54.C7
INT: J5.1, R1.1, U1.A3
INT1: J8.1, R10.1, U2.A3
INT2: J13.1, R17.1, U3.A3
INT3: J18.1, R24.1, U4.A3
INT4: J23.1, R31.1, U5.A3
INT5: J28.1, R38.1, U6.A3
INT6: J33.1, R45.1, U7.A3
INT7: J38.1, R52.1, U8.A3
INT8: J43.1, R59.1, U9.A3
INT9: J48.1, R66.1, U10.A3
INT10: J53.1, R73.1, U11.A3
INT11: J58.1, R80.1, U12.A3
INT12: J63.1, R87.1, U13.A3
INT13: J68.1, R94.1, U14.A3
INT14: J73.1, R101.1, U15.A3
INT15: J78.1, R108.1, U16.A3
INT16: J83.1, R115.1, U17.A3
INT17: J88.1, R122.1, U18.A3
INT18: J93.1, R129.1, U19.A3
INT19: J98.1, R136.1, U20.A3
INT20: J103.1, R143.1, U21.A3
INT21: J108.1, R150.1, U22.A3
INT22: J113.1, R157.1, U23.A3
INT23: J118.1, R164.1, U24.A3
INT24: J123.1, R171.1, U25.A3
INT25: J128.1, R178.1, U26.A3
INT26: J133.1, R185.1, U27.A3
INT27: J138.1, R192.1, U28.A3
INT28: J143.1, R199.1, U29.A3
INT29: J148.1, R206.1, U30.A3
INT30: J153.1, R213.1, U31.A3
INT31: J158.1, R220.1, U32.A3
INT32: J163.1, R227.1, U33.A3
INT33: J168.1, R234.1, U34.A3
INT34: J173.1, R241.1, U35.A3
INT35: J178.1, R248.1, U36.A3
INT36: J183.1, R255.1, U37.A3
INT37: J188.1, R262.1, U38.A3
INT38: J193.1, R269.1, U39.A3
INT39: J198.1, R276.1, U40.A3
INT40: J203.1, R283.1, U41.A3
INT41: J208.1, R290.1, U42.A3
INT42: J213.1, R297.1, U43.A3
INT43: J218.1, R304.1, U44.A3
INT44: J223.1, R311.1, U45.A3
INT45: J228.1, R318.1, U46.A3
INT46: J233.1, R325.1, U47.A3
INT47: J238.1, R332.1, U48.A3
INT48: J243.1, R339.1, U49.A3
INT49: J248.1, R346.1, U50.A3
INT50: J253.1, R353.1, U51.A3
INT51: J258.1, R360.1, U52.A3
INT52: J263.1, R367.1, U53.A3
INT53: J268.1, R374.1, U54.A3
unnamed: I2C.1, R5.2
unnamed: I2C.3, R4.2
unnamed: D1.A, R3.1
unnamed: JP9.1, R1.2
unnamed: JP7.1, R3.2
unnamed: R7.1, U1.C2
unnamed: I2C1.1, R9.2
unnamed: I2C1.3, R8.2
unnamed: JP13.1, R10.2
unnamed: D2.A, R12.1
unnamed: JP14.1, R12.2
unnamed: R14.1, U2.C2
unnamed: I2C2.1, R16.2
unnamed: I2C2.3, R15.2
unnamed: JP21.1, R17.2
unnamed: D3.A, R19.1
unnamed: JP22.1, R19.2
unnamed: R21.1, U3.C2
unnamed: I2C3.1, R23.2
unnamed: I2C3.3, R22.2
unnamed: JP29.1, R24.2
unnamed: D4.A, R26.1
unnamed: JP30.1, R26.2
unnamed: R28.1, U4.C2
unnamed: I2C4.1, R30.2
unnamed: I2C4.3, R29.2
unnamed: JP37.1, R31.2
unnamed: D5.A, R33.1
unnamed: JP38.1, R33.2
unnamed: R35.1, U5.C2
unnamed: I2C5.1, R37.2
unnamed: I2C5.3, R36.2
unnamed: JP45.1, R38.2
unnamed: D6.A, R40.1
unnamed: JP46.1, R40.2
unnamed: R42.1, U6.C2
unnamed: I2C6.1, R44.2
unnamed: I2C6.3, R43.2
unnamed: JP53.1, R45.2
unnamed: D7.A, R47.1
unnamed: JP54.1, R47.2
unnamed: R49.1, U7.C2
unnamed: I2C7.1, R51.2
unnamed: I2C7.3, R50.2
unnamed: JP61.1, R52.2
unnamed: D8.A, R54.1
unnamed: JP62.1, R54.2
unnamed: R56.1, U8.C2
unnamed: I2C8.1, R58.2
unnamed: I2C8.3, R57.2
unnamed: JP69.1, R59.2
unnamed: D9.A, R61.1
unnamed: JP70.1, R61.2
unnamed: R63.1, U9.C2
unnamed: I2C9.1, R65.2
unnamed: I2C9.3, R64.2
unnamed: JP77.1, R66.2
unnamed: D10.A, R68.1
unnamed: JP78.1, R68.2
unnamed: R70.1, U10.C2
unnamed: I2C10.1, R72.2
unnamed: I2C10.3, R71.2
unnamed: JP85.1, R73.2
unnamed: D11.A, R75.1
unnamed: JP86.1, R75.2
unnamed: R77.1, U11.C2
unnamed: I2C11.1, R79.2
unnamed: I2C11.3, R78.2
unnamed: JP93.1, R80.2
unnamed: D12.A, R82.1
unnamed: JP94.1, R82.2
unnamed: R84.1, U12.C2
unnamed: I2C12.1, R86.2
unnamed: I2C12.3, R85.2
unnamed: JP101.1, R87.2
unnamed: D13.A, R89.1
unnamed: JP102.1, R89.2
unnamed: R91.1, U13.C2
unnamed: I2C13.1, R93.2
unnamed: I2C13.3, R92.2
unnamed: JP109.1, R94.2
unnamed: D14.A, R96.1
unnamed: JP110.1, R96.2
unnamed: R98.1, U14.C2
unnamed: I2C14.1, R100.2
unnamed: I2C14.3, R99.2
unnamed: JP117.1, R101.2
unnamed: D15.A, R103.1
unnamed: JP118.1, R103.2
unnamed: R105.1, U15.C2
unnamed: I2C15.1, R107.2
unnamed: I2C15.3, R106.2
unnamed: JP125.1, R108.2
unnamed: D16.A, R110.1
unnamed: JP126.1, R110.2
unnamed: R112.1, U16.C2
unnamed: I2C16.1, R114.2
unnamed: I2C16.3, R113.2
unnamed: JP133.1, R115.2
unnamed: D17.A, R117.1
unnamed: JP134.1, R117.2
unnamed: R119.1, U17.C2
unnamed: I2C17.1, R121.2
unnamed: I2C17.3, R120.2
unnamed: JP141.1, R122.2
unnamed: D18.A, R124.1
unnamed: JP142.1, R124.2
unnamed: R126.1, U18.C2
unnamed: I2C18.1, R128.2
unnamed: I2C18.3, R127.2
unnamed: JP149.1, R129.2
unnamed: D19.A, R131.1
unnamed: JP150.1, R131.2
unnamed: R133.1, U19.C2
unnamed: I2C19.1, R135.2
unnamed: I2C19.3, R134.2
unnamed: JP157.1, R136.2
unnamed: D20.A, R138.1
unnamed: JP158.1, R138.2
unnamed: R140.1, U20.C2
unnamed: I2C20.1, R142.2
unnamed: I2C20.3, R141.2
unnamed: JP165.1, R143.2
unnamed: D21.A, R145.1
unnamed: JP166.1, R145.2
unnamed: R147.1, U21.C2
unnamed: I2C21.1, R149.2
unnamed: I2C21.3, R148.2
unnamed: JP173.1, R150.2
unnamed: D22.A, R152.1
unnamed: JP174.1, R152.2
unnamed: R154.1, U22.C2
unnamed: I2C22.1, R156.2
unnamed: I2C22.3, R155.2
unnamed: JP181.1, R157.2
unnamed: D23.A, R159.1
unnamed: JP182.1, R159.2
unnamed: R161.1, U23.C2
unnamed: I2C23.1, R163.2
unnamed: I2C23.3, R162.2
unnamed: JP189.1, R164.2
unnamed: D24.A, R166.1
unnamed: JP190.1, R166.2
unnamed: R168.1, U24.C2
unnamed: I2C24.1, R170.2
unnamed: I2C24.3, R169.2
unnamed: JP197.1, R171.2
unnamed: D25.A, R173.1
unnamed: JP198.1, R173.2
unnamed: R175.1, U25.C2
unnamed: I2C25.1, R177.2
unnamed: I2C25.3, R176.2
unnamed: JP205.1, R178.2
unnamed: D26.A, R180.1
unnamed: JP206.1, R180.2
unnamed: R182.1, U26.C2
unnamed: I2C26.1, R184.2
unnamed: I2C26.3, R183.2
unnamed: JP213.1, R185.2
unnamed: D27.A, R187.1
unnamed: JP214.1, R187.2
unnamed: R189.1, U27.C2
unnamed: I2C27.1, R191.2
unnamed: I2C27.3, R190.2
unnamed: JP221.1, R192.2
unnamed: D28.A, R194.1
unnamed: JP222.1, R194.2
unnamed: R196.1, U28.C2
unnamed: I2C28.1, R198.2
unnamed: I2C28.3, R197.2
unnamed: JP229.1, R199.2
unnamed: D29.A, R201.1
unnamed: JP230.1, R201.2
unnamed: R203.1, U29.C2
unnamed: I2C29.1, R205.2
unnamed: I2C29.3, R204.2
unnamed: JP237.1, R206.2
unnamed: D30.A, R208.1
unnamed: JP238.1, R208.2
unnamed: R210.1, U30.C2
unnamed: I2C30.1, R212.2
unnamed: I2C30.3, R211.2
unnamed: JP245.1, R213.2
unnamed: D31.A, R215.1
unnamed: JP246.1, R215.2
unnamed: R217.1, U31.C2
unnamed: I2C31.1, R219.2
unnamed: I2C31.3, R218.2
unnamed: JP253.1, R220.2
unnamed: D32.A, R222.1
unnamed: JP254.1, R222.2
unnamed: R224.1, U32.C2
unnamed: I2C32.1, R226.2
unnamed: I2C32.3, R225.2
unnamed: JP261.1, R227.2
unnamed: D33.A, R229.1
unnamed: JP262.1, R229.2
unnamed: R231.1, U33.C2
unnamed: I2C33.1, R233.2
unnamed: I2C33.3, R232.2
unnamed: JP269.1, R234.2
unnamed: D34.A, R236.1
unnamed: JP270.1, R236.2
unnamed: R238.1, U34.C2
unnamed: I2C34.1, R240.2
unnamed: I2C34.3, R239.2
unnamed: JP277.1, R241.2
unnamed: D35.A, R243.1
unnamed: JP278.1, R243.2
unnamed: R245.1, U35.C2
unnamed: I2C35.1, R247.2
unnamed: I2C35.3, R246.2
unnamed: JP285.1, R248.2
unnamed: D36.A, R250.1
unnamed: JP286.1, R250.2
unnamed: R252.1, U36.C2
unnamed: I2C36.1, R254.2
unnamed: I2C36.3, R253.2
unnamed: JP293.1, R255.2
unnamed: D37.A, R257.1
unnamed: JP294.1, R257.2
unnamed: R259.1, U37.C2
unnamed: I2C37.1, R261.2
unnamed: I2C37.3, R260.2
unnamed: JP301.1, R262.2
unnamed: D38.A, R264.1
unnamed: JP302.1, R264.2
unnamed: R266.1, U38.C2
unnamed: I2C38.1, R268.2
unnamed: I2C38.3, R267.2
unnamed: JP309.1, R269.2
unnamed: D39.A, R271.1
unnamed: JP310.1, R271.2
unnamed: R273.1, U39.C2
unnamed: I2C39.1, R275.2
unnamed: I2C39.3, R274.2
unnamed: JP317.1, R276.2
unnamed: D40.A, R278.1
unnamed: JP318.1, R278.2
unnamed: R280.1, U40.C2
unnamed: I2C40.1, R282.2
unnamed: I2C40.3, R281.2
unnamed: JP325.1, R283.2
unnamed: D41.A, R285.1
unnamed: JP326.1, R285.2
unnamed: R287.1, U41.C2
unnamed: I2C41.1, R289.2
unnamed: I2C41.3, R288.2
unnamed: JP333.1, R290.2
unnamed: D42.A, R292.1
unnamed: JP334.1, R292.2
unnamed: R294.1, U42.C2
unnamed: I2C42.1, R296.2
unnamed: I2C42.3, R295.2
unnamed: JP341.1, R297.2
unnamed: D43.A, R299.1
unnamed: JP342.1, R299.2
unnamed: R301.1, U43.C2
unnamed: I2C43.1, R303.2
unnamed: I2C43.3, R302.2
unnamed: JP349.1, R304.2
unnamed: D44.A, R306.1
unnamed: JP350.1, R306.2
unnamed: R308.1, U44.C2
unnamed: I2C44.1, R310.2
unnamed: I2C44.3, R309.2
unnamed: JP357.1, R311.2
unnamed: D45.A, R313.1
unnamed: JP358.1, R313.2
unnamed: R315.1, U45.C2
unnamed: I2C45.1, R317.2
unnamed: I2C45.3, R316.2
unnamed: JP365.1, R318.2
unnamed: D46.A, R320.1
unnamed: JP366.1, R320.2
unnamed: R322.1, U46.C2
unnamed: I2C46.1, R324.2
unnamed: I2C46.3, R323.2
unnamed: JP373.1, R325.2
unnamed: D47.A, R327.1
unnamed: JP374.1, R327.2
unnamed: R329.1, U47.C2
unnamed: I2C47.1, R331.2
unnamed: I2C47.3, R330.2
unnamed: JP381.1, R332.2
unnamed: D48.A, R334.1
unnamed: JP382.1, R334.2
unnamed: R336.1, U48.C2
unnamed: I2C48.1, R338.2
unnamed: I2C48.3, R337.2
unnamed: JP389.1, R339.2
unnamed: D49.A, R341.1
unnamed: JP390.1, R341.2
unnamed: R343.1, U49.C2
unnamed: I2C49.1, R345.2
unnamed: I2C49.3, R344.2
unnamed: JP397.1, R346.2
unnamed: D50.A, R348.1
unnamed: JP398.1, R348.2
unnamed: R350.1, U50.C2
unnamed: I2C50.1, R352.2
unnamed: I2C50.3, R351.2
unnamed: JP405.1, R353.2
unnamed: D51.A, R355.1
unnamed: JP406.1, R355.2
unnamed: R357.1, U51.C2
unnamed: I2C51.1, R359.2
unnamed: I2C51.3, R358.2
unnamed: JP413.1, R360.2
unnamed: D52.A, R362.1
unnamed: JP414.1, R362.2
unnamed: R364.1, U52.C2
unnamed: I2C52.1, R366.2
unnamed: I2C52.3, R365.2
unnamed: JP421.1, R367.2
unnamed: D53.A, R369.1
unnamed: JP422.1, R369.2
unnamed: R371.1, U53.C2
unnamed: I2C53.1, R373.2
unnamed: I2C53.3, R372.2
unnamed: JP429.1, R374.2
unnamed: D54.A, R376.1
unnamed: JP430.1, R376.2
unnamed: R378.1, U54.C2
RST: J6.1, R6.1, U1.A1
RST1: J9.1, R13.1, U2.A1
RST2: J14.1, R20.1, U3.A1
RST3: J19.1, R27.1, U4.A1
RST4: J24.1, R34.1, U5.A1
RST5: J29.1, R41.1, U6.A1
RST6: J34.1, R48.1, U7.A1
RST7: J39.1, R55.1, U8.A1
RST8: J44.1, R62.1, U9.A1
RST9: J49.1, R69.1, U10.A1
RST10: J54.1, R76.1, U11.A1
RST11: J59.1, R83.1, U12.A1
RST12: J64.1, R90.1, U13.A1
RST13: J69.1, R97.1, U14.A1
RST14: J74.1, R104.1, U15.A1
RST15: J79.1, R111.1, U16.A1
RST16: J84.1, R118.1, U17.A1
RST17: J89.1, R125.1, U18.A1
RST18: J94.1, R132.1, U19.A1
RST19: J99.1, R139.1, U20.A1
RST20: J104.1, R146.1, U21.A1
RST21: J109.1, R153.1, U22.A1
RST22: J114.1, R160.1, U23.A1
RST23: J119.1, R167.1, U24.A1
RST24: J124.1, R174.1, U25.A1
RST25: J129.1, R181.1, U26.A1
RST26: J134.1, R188.1, U27.A1
RST27: J139.1, R195.1, U28.A1
RST28: J144.1, R202.1, U29.A1
RST29: J149.1, R209.1, U30.A1
RST30: J154.1, R216.1, U31.A1
RST31: J159.1, R223.1, U32.A1
RST32: J164.1, R230.1, U33.A1
RST33: J169.1, R237.1, U34.A1
RST34: J174.1, R244.1, U35.A1
RST35: J179.1, R251.1, U36.A1
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
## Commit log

2021-11-18 Fix small changes from design review. Add panel.
2021-11-19 Add v10 production files
